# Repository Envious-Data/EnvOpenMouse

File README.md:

# EnvOpenMouse
 An Open-source mouse for the UK market.
 
### Why?

A lot of friends of mine would like something like a ploopyco mouse but there arent such options avaliable here in the UK and even then custom mouses as a whole is just not very popular.

This will be a open source mouse utilizting the PMW3360 and RP2040.

- Why the RP2040? Why not I say
- Why PMW3360 - its easiest to get and is well known by the community meaning resources are avaliable.

### To do
- Need to verify fit of everything
- firmware
- 3d printable housing
- housing/shell maybe can be made of other matierals
- perhaps write a guide on how to order and get everything made
- contact some vendors to sell this through for those who dont want self assembly

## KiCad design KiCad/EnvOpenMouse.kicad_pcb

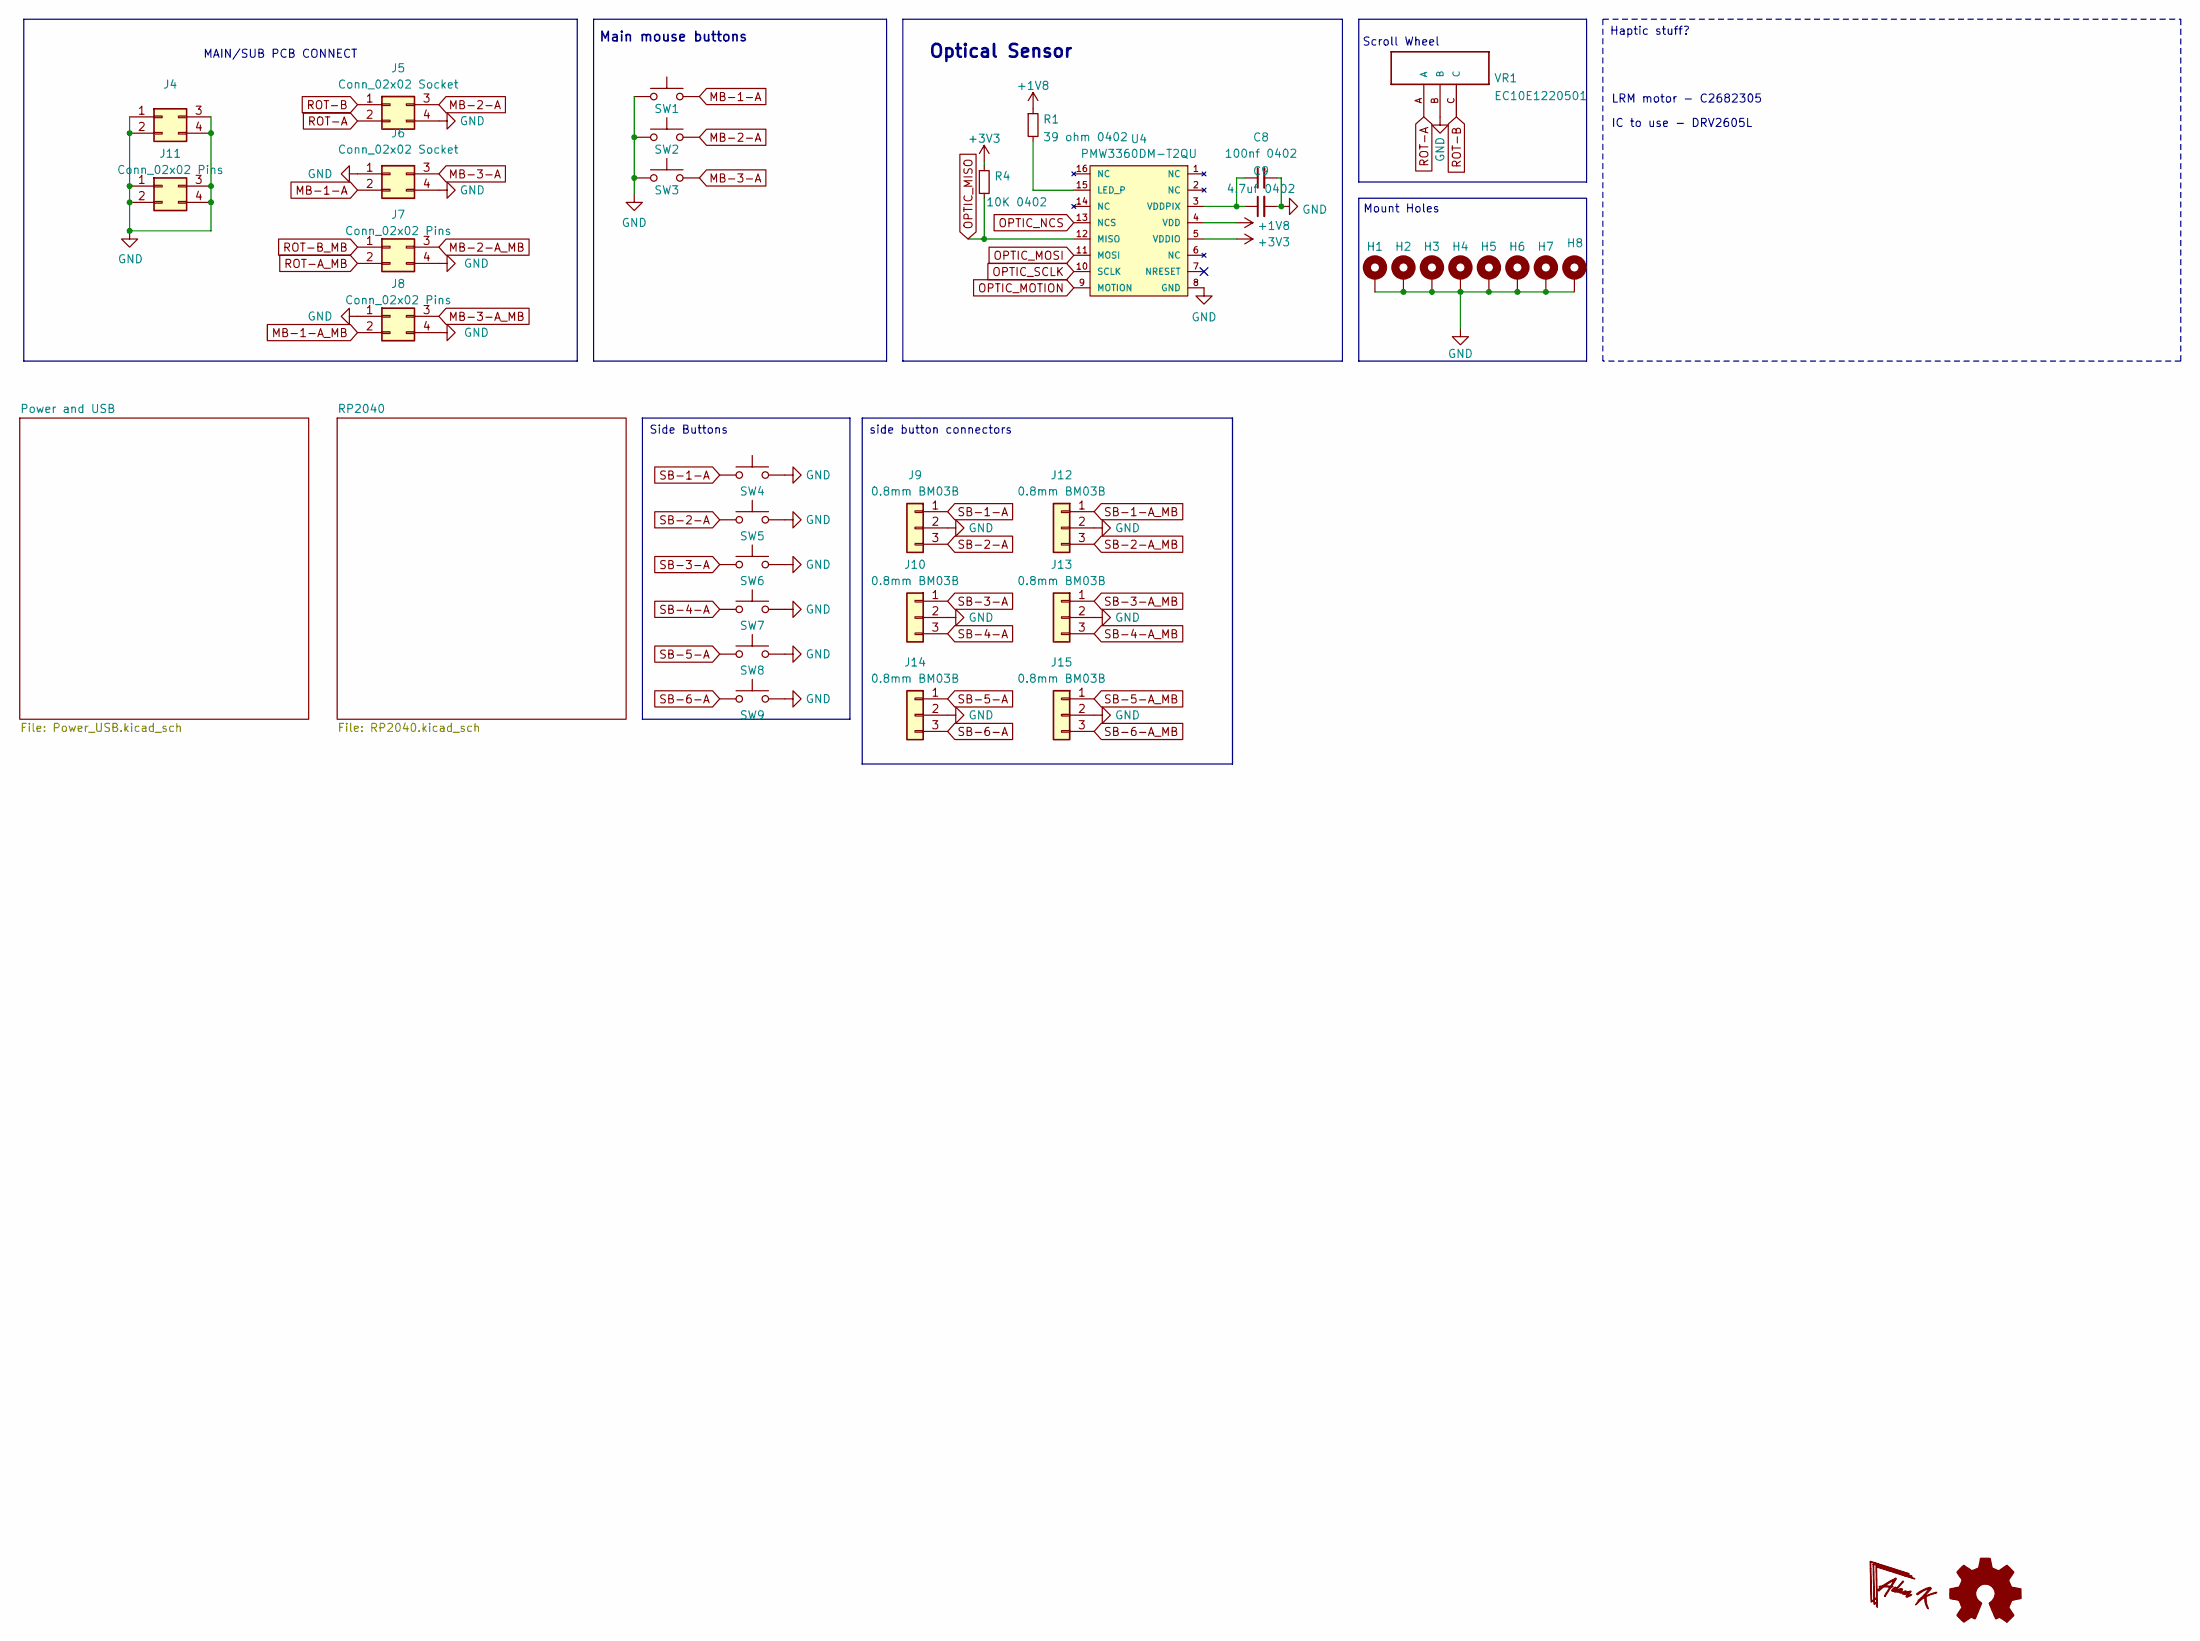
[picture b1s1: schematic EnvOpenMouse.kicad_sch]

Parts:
C8: 100nf 0402; C_0402_1005Metric
C9: 4.7uf 0402; C_0402_1005Metric
H1, H2, H3, H4, H5, H6, H7, H8: MountingHole_Pad; MountingHole_2.2mm_M2
J4: Conn_02x02 Socket; PinSocket_1x02_P1.27mm_Vertical
J5, J6: Conn_02x02 Socket; PinSocket_2x02_P1.27mm_Vertical
J7, J8: Conn_02x02 Pins; PinHeader_2x02_P1.27mm_Vertical
J9, J10, J12, J13, J14, J15: 0.8mm BM03B; JST_SUR_BM03B-SURS-TF_1x03-1MP_P0.80mm_Vertical
J11: Conn_02x02 Pins; PinHeader_1x02_P1.27mm_Vertical
R1: 39 ohm 0402; R_0402_1005Metric
R4: 10K 0402; R_0402_1005Metric
SW1, SW2, SW3: Kailh GM switch; MouseSwitch
SW4, SW5, SW6, SW7, SW8, SW9: B3U-1000P; SW_SPST_B3U-1000P
U4: PMW3360DM-T2QU; DIP-16_W10.16mm
VR1: EC10E1220501; TRIM_EC10E1220501

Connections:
+1V8: R1.1, U4.4 (VDD); also elsewhere on the board
+3V3: R4.1, U4.5 (VDDIO); also elsewhere on the board
GND: C8.2, C9.2, H1.1, H2.1, H3.1, H4.1, H5.1, H6.1, H7.1, H8.1, J4.1, J4.2, J4.3, J4.4, J5.4, J6.1, J6.4, J7.4, J8.1, J8.4, J9.2, J10.2, J11.1, J11.2, J11.3, J11.4, J12.2, J13.2, J14.2, J15.2, SW1.1, SW2.1, SW3.1, SW4.1, SW5.1, SW6.1, SW7.1, SW8.1, SW9.1, U4.8 (GND), VR1.B; also elsewhere on the board
MB-1-A: J6.2, SW1.2
MB-1-A_MB: J8.2; also elsewhere on the board
MB-2-A: J5.3, SW2.2
MB-2-A_MB: J7.3; also elsewhere on the board
MB-3-A: J6.3, SW3.2
MB-3-A_MB: J8.3; also elsewhere on the board
unnamed: R1.2, U4.15 (LED_P)
unnamed: C8.1, C9.1, U4.3 (VDDPIX)
OPTIC_MISO: R4.2, U4.12 (MISO); also elsewhere on the board
OPTIC_MOSI: U4.11 (MOSI); also elsewhere on the board
OPTIC_MOTION: U4.9 (MOTION); also elsewhere on the board
OPTIC_NCS: U4.13 (NCS); also elsewhere on the board
OPTIC_SCLK: U4.10 (SCLK); also elsewhere on the board
ROT-A: J5.2, VR1.A
ROT-A_MB: J7.2; also elsewhere on the board
ROT-B: J5.1, VR1.C
ROT-B_MB: J7.1; also elsewhere on the board
SB-1-A: J9.1, SW4.2
SB-1-A_MB: J12.1; also elsewhere on the board
SB-2-A: J9.3, SW5.2
SB-2-A_MB: J12.3; also elsewhere on the board
SB-3-A: J10.1, SW6.2
SB-3-A_MB: J13.1; also elsewhere on the board
SB-4-A: J10.3, SW7.2
SB-4-A_MB: J13.3; also elsewhere on the board
SB-5-A: J14.1, SW8.2
SB-5-A_MB: J15.1; also elsewhere on the board
SB-6-A: J14.3, SW9.2
SB-6-A_MB: J15.3; also elsewhere on the board

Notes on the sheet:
Side Buttons
side button connectors
Haptic stuff?
MAIN/SUB PCB CONNECT
Scroll Wheel
LRM motor - C2682305
Main mouse buttons
IC to use - DRV2605L
Optical Sensor
Mount Holes

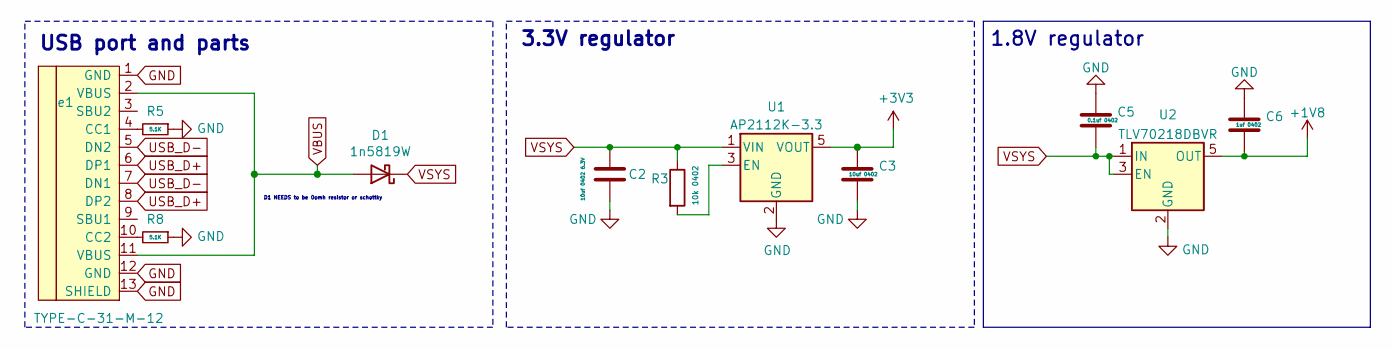
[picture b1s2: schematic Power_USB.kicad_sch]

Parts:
C2: 10uf 0402 6.3V; C_0402_1005Metric
C3: 10uf 0402; C_0402_1005Metric
C5: 0.1uf 0402; C_0402_1005Metric
C6: 1uf 0402; C_0402_1005Metric
D1: 1n5819W; D_SOD-123
R3: 10k 0402; R_0402_1005Metric
R5, R8: 5.1K; R_0402_1005Metric
U1: AP2112K-3.3; SOT-23-5
U2: TLV70218DBVR; SOT-23-5
e1: TYPE-C-31-M-12; HRO-TYPE-C-31-M-12

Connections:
+1V8: C6.2, U2.5 (OUT); also elsewhere on the board
+3V3: C3.1, U1.5 (VOUT); also elsewhere on the board
GND: C2.2, C3.2, C5.1, C6.1, R5.1, R8.1, U1.2 (GND), U2.2 (GND), e1.1 (GND), e1.12 (GND), e1.13 (SHIELD); also elsewhere on the board
unnamed: R3.2, U1.3 (EN)
unnamed: R5.2, e1.4 (CC1)
unnamed: R8.2, e1.10 (CC2)
USB_D+: e1.6 (DP1), e1.8 (DP2); also elsewhere on the board
USB_D-: e1.5 (DN2), e1.7 (DN1); also elsewhere on the board
VBUS: D1.2 (A), e1.2 (VBUS), e1.11 (VBUS)
VSYS: C2.1, C5.2, D1.1 (K), R3.1, U1.1 (VIN), U2.1 (IN), U2.3 (EN)

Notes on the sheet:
1.8V regulator
3.3V regulator
USB port and parts
D1 NEEDS to be 0omh resistor or schottky

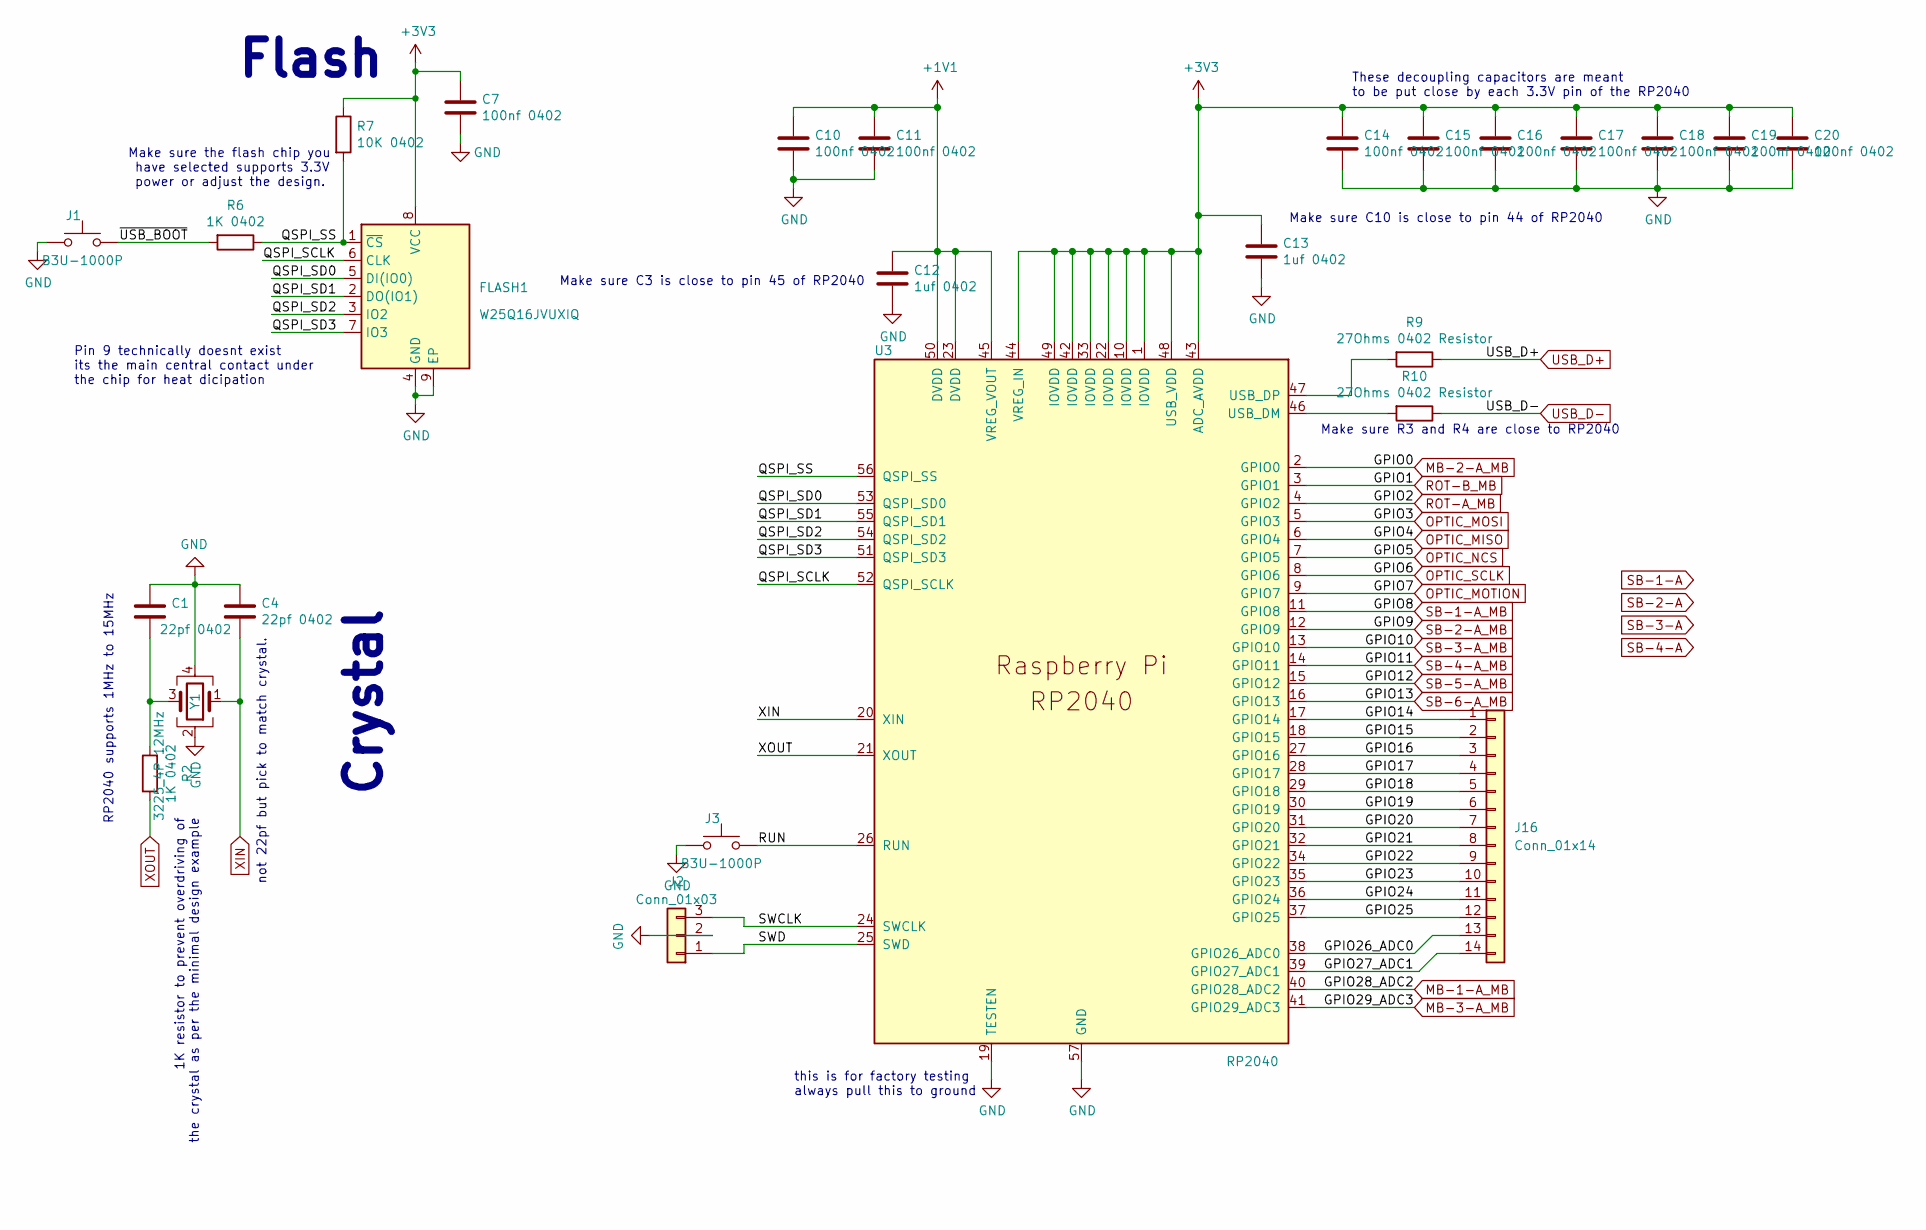
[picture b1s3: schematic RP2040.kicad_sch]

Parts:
C1, C4: 22pf 0402; C_0402_1005Metric
C7, C10, C11, C14, C15, C16, C17, C18, C19, C20: 100nf 0402; C_0402_1005Metric
C12, C13: 1uf 0402; C_0402_1005Metric
FLASH1: W25Q16JVUXIQ; SON-8-1EP_3x2mm_P0.5mm_EP1.4x1.6mm
J1, J3: B3U-1000P; SW_Push_SPST_NO_Alps_SKRK
J2: Conn_01x03; PinHeader_1x03_P1.27mm_Vertical
J16: Conn_01x14; PinHeader_1x14_P1.00mm_Vertical
R2, R6: 1K 0402; R_0402_1005Metric
R7: 10K 0402; R_0402_1005Metric
R9, R10: 27Ohms 0402 Resistor; C_0402_1005Metric
U3: RP2040; RP2040-QFN-56
Y1: 3225_4P 12MHz; Crystal_SMD_3225-4Pin_3.2x2.5mm

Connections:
+1V1: C10.1, C11.1, C12.1, U3.23 (DVDD), U3.45 (VREG_VOUT), U3.50 (DVDD)
+3V3: C7.1, C13.1, C14.1, C15.1, C16.1, C17.1, C18.1, C19.1, C20.1, FLASH1.8 (VCC), R7.1, U3.1 (IOVDD), U3.10 (IOVDD), U3.22 (IOVDD), U3.33 (IOVDD), U3.42 (IOVDD), U3.43 (ADC_AVDD), U3.44 (VREG_IN), U3.48 (USB_VDD), U3.49 (IOVDD); also elsewhere on the board
/RP2040/GPIO14: J16.1, U3.17 (GPIO14)
/RP2040/GPIO15: J16.2, U3.18 (GPIO15)
/RP2040/GPIO16: J16.3, U3.27 (GPIO16)
/RP2040/GPIO17: J16.4, U3.28 (GPIO17)
/RP2040/GPIO18: J16.5, U3.29 (GPIO18)
/RP2040/GPIO19: J16.6, U3.30 (GPIO19)
/RP2040/GPIO20: J16.7, U3.31 (GPIO20)
/RP2040/GPIO21: J16.8, U3.32 (GPIO21)
/RP2040/GPIO22: J16.9, U3.34 (GPIO22)
/RP2040/GPIO23: J16.10, U3.35 (GPIO23)
/RP2040/GPIO24: J16.11, U3.36 (GPIO24)
/RP2040/GPIO25: J16.12, U3.37 (GPIO25)
/RP2040/GPIO26_ADC0: J16.13, U3.38 (GPIO26_ADC0)
/RP2040/GPIO27_ADC1: J16.14, U3.39 (GPIO27_ADC1)
/RP2040/QSPI_SCLK: FLASH1.6 (CLK), U3.52 (QSPI_SCLK)
/RP2040/QSPI_SD0: FLASH1.5 (DI(IO0)), U3.53 (QSPI_SD0)
/RP2040/QSPI_SD1: FLASH1.2 (DO(IO1)), U3.55 (QSPI_SD1)
/RP2040/QSPI_SD2: FLASH1.3 (IO2), U3.54 (QSPI_SD2)
/RP2040/QSPI_SD3: FLASH1.7 (IO3), U3.51 (QSPI_SD3)
/RP2040/QSPI_SS: FLASH1.1 (~CS), R6.1, R7.2, U3.56 (QSPI_SS)
/RP2040/RUN: J3.1, U3.26 (RUN)
/RP2040/SWCLK: J2.3, U3.24 (SWCLK)
/RP2040/SWD: J2.1, U3.25 (SWD)
/RP2040/~USB_BOOT: J1.1, R6.2
GND: C1.1, C4.1, C7.2, C10.2, C11.2, C12.2, C13.2, C14.2, C15.2, C16.2, C17.2, C18.2, C19.2, C20.2, FLASH1.4 (GND), FLASH1.9 (EP), J1.2, J2.2, J3.2, U3.19 (TESTEN), U3.57 (GND), Y1.2, Y1.4; also elsewhere on the board
MB-1-A_MB: U3.40 (GPIO28_ADC2); also elsewhere on the board
MB-2-A_MB: U3.2 (GPIO0); also elsewhere on the board
MB-3-A_MB: U3.41 (GPIO29_ADC3); also elsewhere on the board
unnamed: C1.2, R2.2, Y1.3
unnamed: R10.2, U3.46 (USB_DM)
unnamed: R9.2, U3.47 (USB_DP)
OPTIC_MISO: U3.6 (GPIO4); also elsewhere on the board
OPTIC_MOSI: U3.5 (GPIO3); also elsewhere on the board
OPTIC_MOTION: U3.9 (GPIO7); also elsewhere on the board
OPTIC_NCS: U3.7 (GPIO5); also elsewhere on the board
OPTIC_SCLK: U3.8 (GPIO6); also elsewhere on the board
ROT-A_MB: U3.4 (GPIO2); also elsewhere on the board
ROT-B_MB: U3.3 (GPIO1); also elsewhere on the board
SB-1-A_MB: U3.11 (GPIO8); also elsewhere on the board
SB-2-A_MB: U3.12 (GPIO9); also elsewhere on the board
SB-3-A_MB: U3.13 (GPIO10); also elsewhere on the board
SB-4-A_MB: U3.14 (GPIO11); also elsewhere on the board
SB-5-A_MB: U3.15 (GPIO12); also elsewhere on the board
SB-6-A_MB: U3.16 (GPIO13); also elsewhere on the board
USB_D+: R9.1; also elsewhere on the board
USB_D-: R10.1; also elsewhere on the board
XIN: C4.2, U3.20 (XIN), Y1.1
XOUT: R2.1, U3.21 (XOUT)

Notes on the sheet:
Make sure C10 is close to pin 44 of RP2040
1K resistor to prevent overdriving of the crystal as per the minimal design example
Crystal
Make sure R3 and R4 are close to RP2040
this is for factory testing always pull this to ground
Make sure C3 is close to pin 45 of RP2040
Pin 9 technically doesnt exist its the main central contact under the chip for heat dicipation
not 22pf but pick to match crystal.
These decoupling capacitors are meant to be put close by each 3.3V pin of the RP2040
Make sure the flash chip you have selected supports 3.3V power or adjust the design.
Flash
RP2040 supports 1MHz to 15MHz

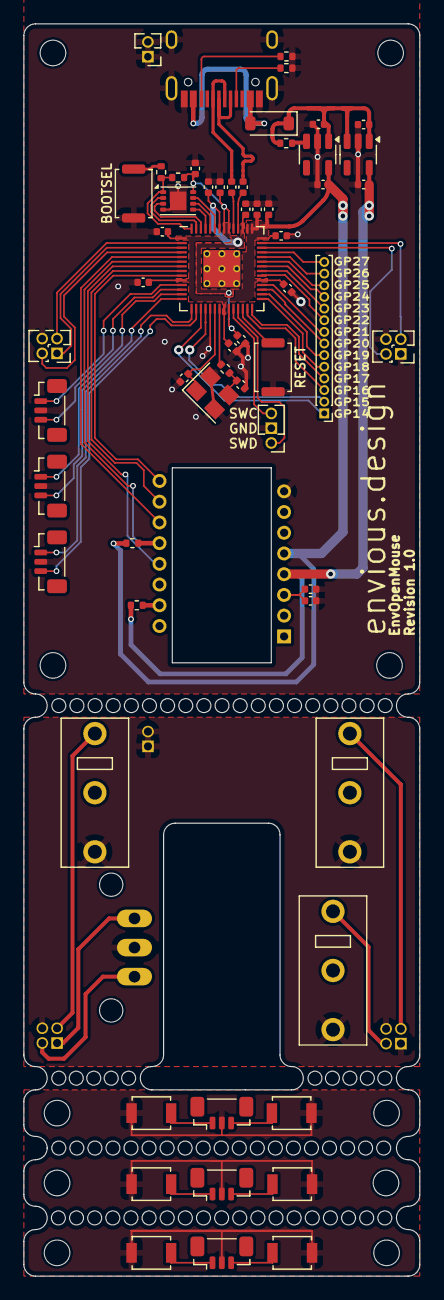
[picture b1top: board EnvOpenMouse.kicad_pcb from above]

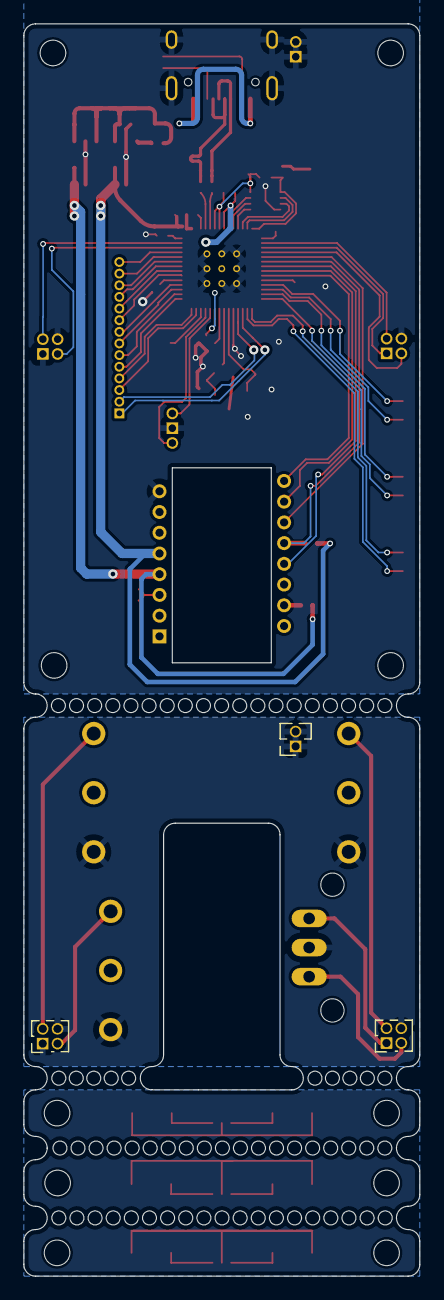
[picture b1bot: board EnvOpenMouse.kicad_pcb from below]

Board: 2 copper layers, 34.0 x 107.5 mm, 74 parts (3 on the bottom side), 69 nets.

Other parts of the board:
H5#2, H6#2: MountingHole_Pad; MountingHole_2.2mm_M2

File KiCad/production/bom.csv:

Designator,Footprint,Quantity,Value,LCSC Part #
"C1, C4",0402,2,22pf 0402, 
"C10, C11, C14, C15, C16, C17, C18, C19, C20, C8",0402,10,100nf 0402,
"C12, C13, C6",0402,3,1uf 0402,
C2,0402,1,10uf 0402 6.3V,
C3,0402,1,10uf 0402,
C5,0402,1,0.1uf 0402,
C7,0402,1,100nf 0402, 
C9,0402,1,4.7uf 0402,
D1,D_SOD-123,1,1n4002W,
FLASH1,SON-8-1EP_3x2mm_P0.5mm_EP1.4x1.6mm,1,W25Q16JVUXIQ,
"H1, H2, H3, H4, H5_2, H5, H6_2, H6, H7, H8",MountingHole_2.2mm_M2,10,MountingHole_Pad,
J1,SW_Push_SPST_NO_Alps_SKRK,1,Button, 
"J10, J12, J13, J14, J15, J9",JST_SUR_BM03B-SURS-TF_1x03-1MP_P0.80mm_Vertical,6,0.8mm BM03B,
"J11, J4",PinHeader_1x02_P1.27mm_Vertical,2,Conn_02x02_Top_Bottom,
J16,PinHeader_1x14_P1.00mm_Vertical,1,Conn_01x14,
J2,PinHeader_1x03_P1.27mm_Vertical,1,Conn_01x03,
J3,SW_Push_SPST_NO_Alps_SKRK,1,Button,
"J5, J6, J7, J8",PinHeader_2x02_P1.27mm_Vertical,4,Conn_02x02_Top_Bottom,
R1,0402,1,39 ohm 0402,
R10,0402,1,27Ohms 0402 Resistor,
"R2, R6",0402,2,1K 0402, 
"R3, R4",0402,2,10k 0402,
"R5, R8",0402,2,5.1K,
R7,0402,1,10K 0402,  
R9,0402,1,27Ohms  0402 Resistor,
"SW1, SW2, SW3",MouseSwitch,3,SW_Push_SPDT,
"SW4, SW5, SW6, SW7, SW8, SW9",SW_SPST_B3U-1000P,6,SW_Push_SPDT,
U1,SOT-23-5,1,AP2112K-3.3,
U2,SOT-23-5,1,TLV70218DBVR,
U3,RP2040-QFN-56,1,RP2040,
U4,DIP-16_W10.16mm,1,PMW3360DM-T2QU,
VR1,TRIM_EC10E1220501,1,EC10E1220501,
Y1,Crystal_SMD_3225-4Pin_3.2x2.5mm,1,3225_4P 12MHz, 
e1,HRO-TYPE-C-31-M-12,1,TYPE-C-31-M-12,

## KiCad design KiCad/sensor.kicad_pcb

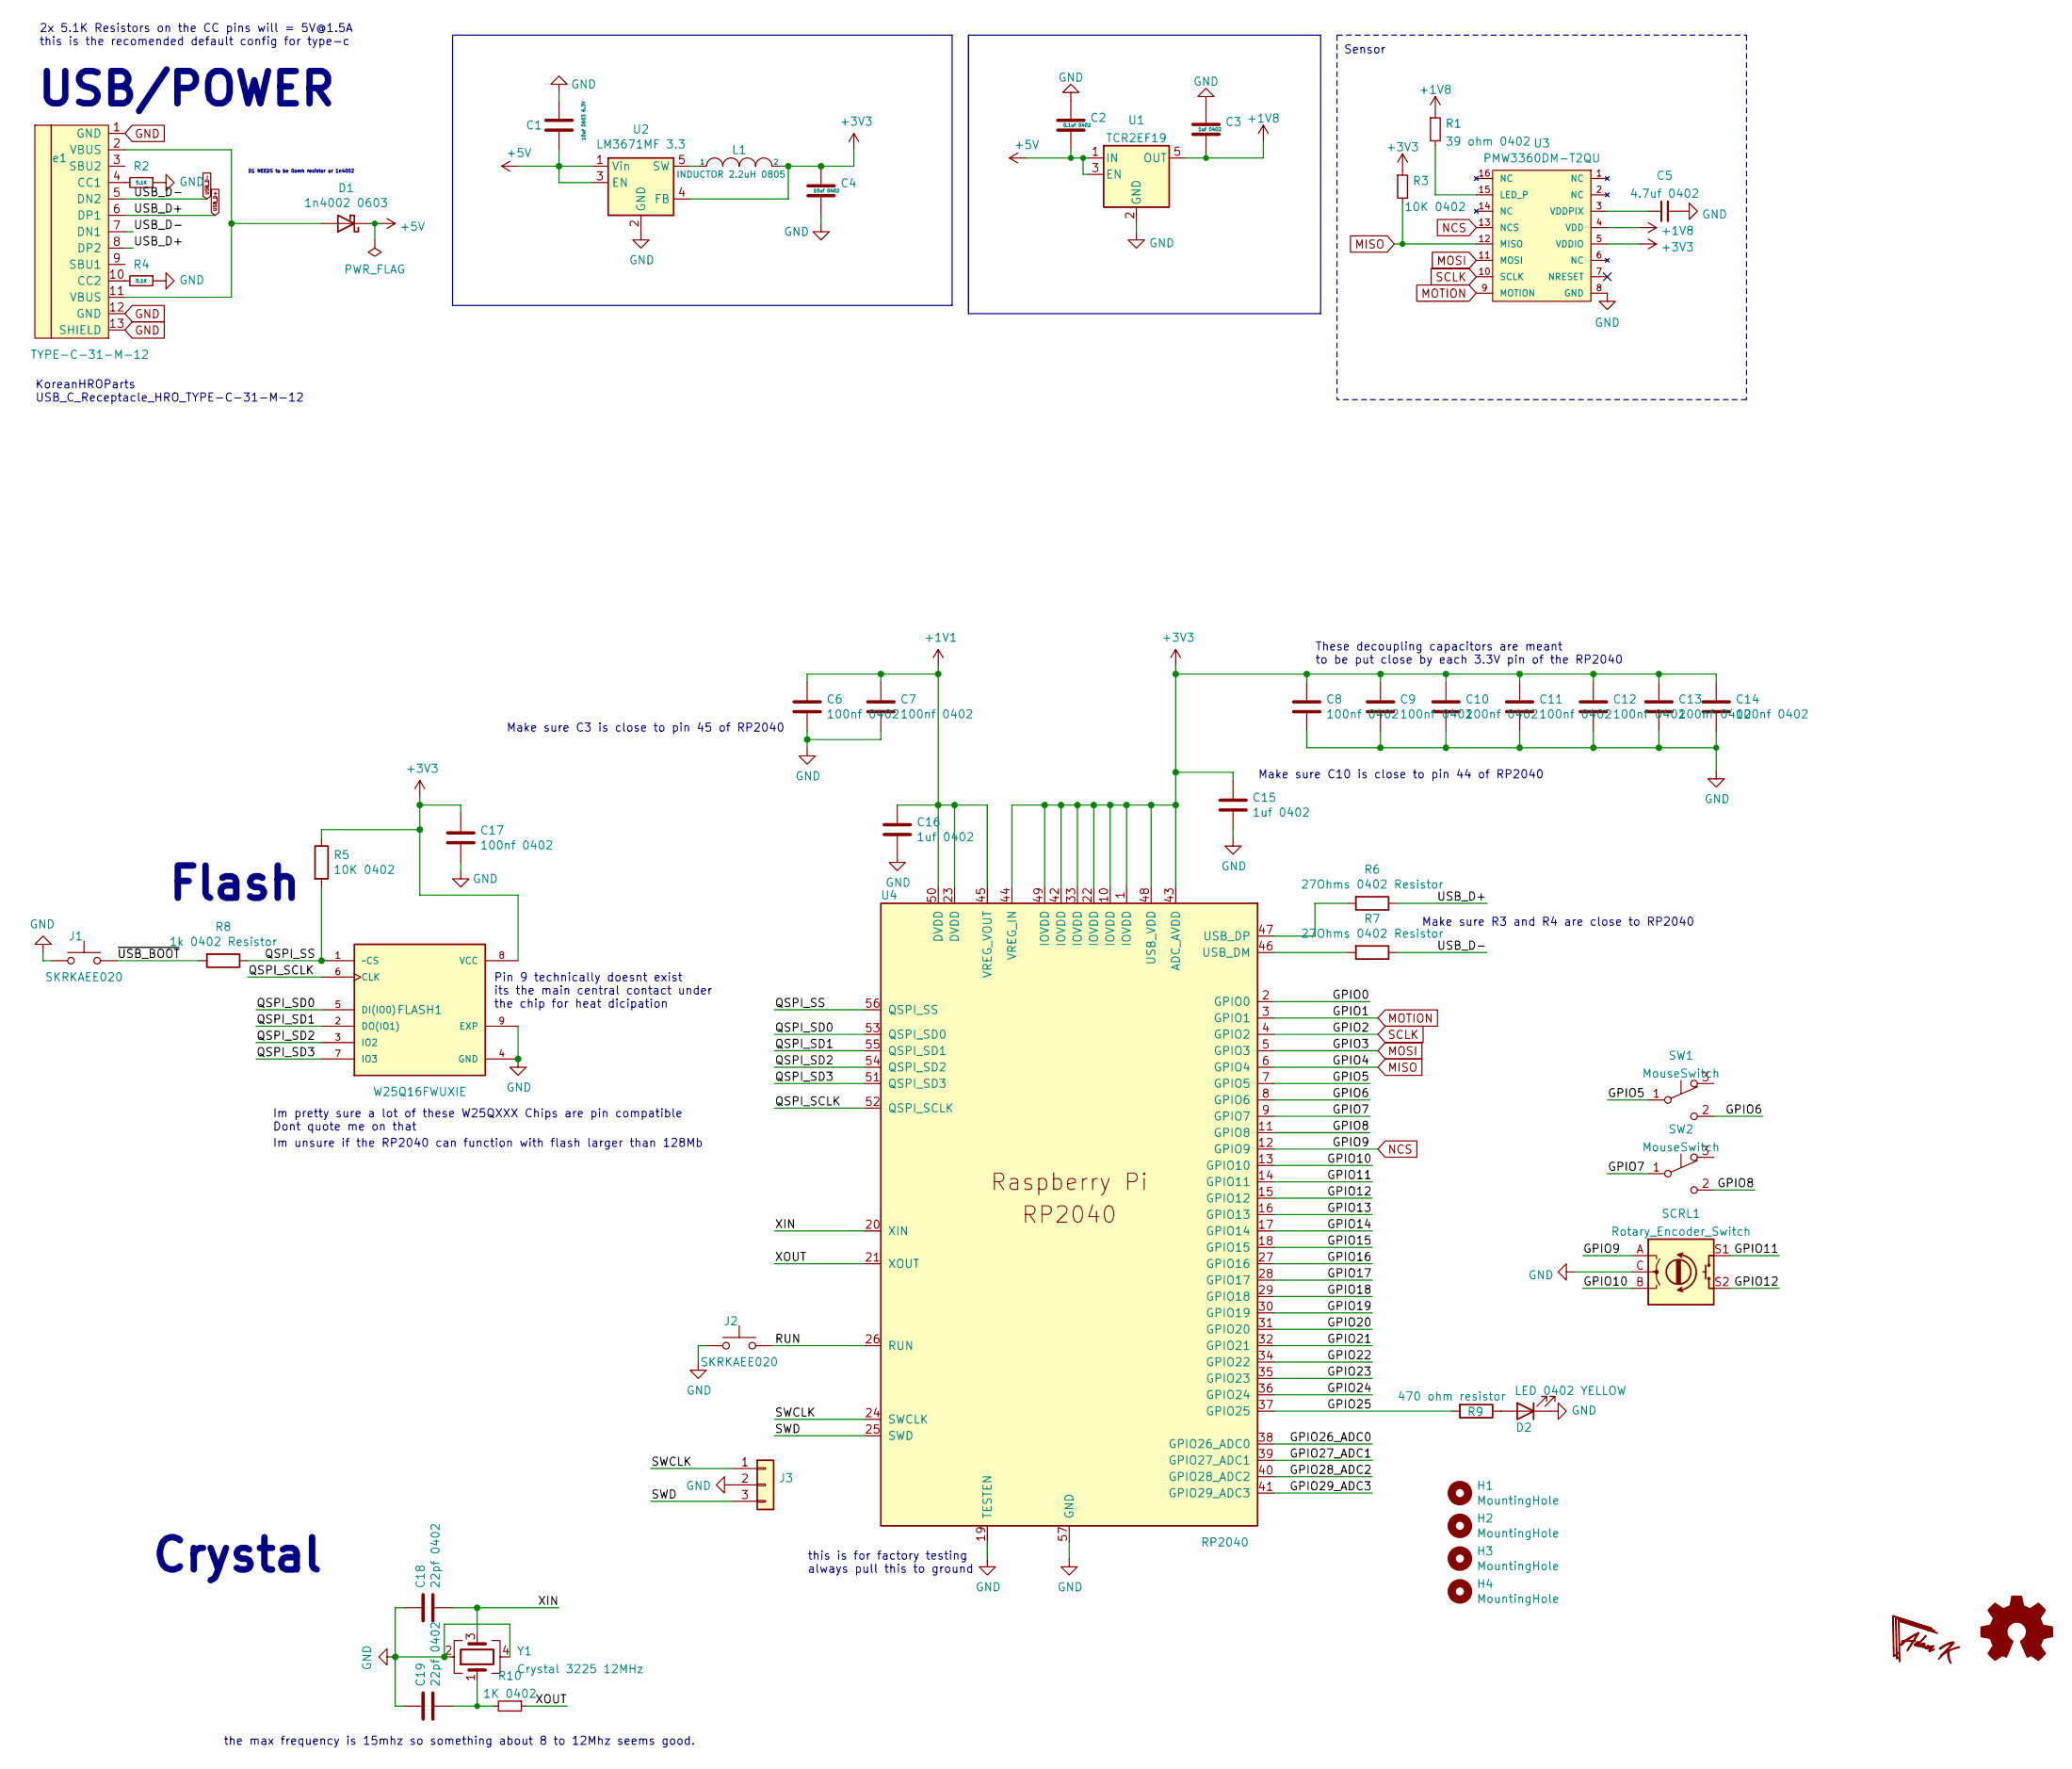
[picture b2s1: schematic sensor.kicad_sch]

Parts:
C1: 10uf 0603 6.3V; C_0603_1608Metric
C2: 0.1uf 0402; C_0402_1005Metric
C3, C15, C16: 1uf 0402; C_0402_1005Metric
C4: 10uf 0402; C_0402_1005Metric
C5: 4.7uf 0402; C_0402_1005Metric
C6, C7, C8, C9, C10, C11, C12, C13, C14, C17: 100nf 0402; C_0402_1005Metric
C18, C19: 22pf 0402; C_0402_1005Metric
D1: 1n4002 0603; D_0603_1608Metric
D2: LED 0402 YELLOW; LED_0402_1005Metric
FLASH1: W25Q16FWUXIE; SON-8-1EP_3x2mm_P0.5mm_EP1.4x1.6mm
H1, H2, H3, H4: MountingHole; MountingHole_2.2mm_M2
J1, J2: SKRKAEE020; SW_Push_SPST_NO_Alps_SKRK
J3: Conn_01x03_Male; PinHeader_1x03_P2.54mm_Vertical
L1: INDUCTOR 2.2uH 0805; L_0805_2012Metric
R1: 39 ohm 0402; R_0402_1005Metric
R2, R4: 5.1K; R_0402_1005Metric
R3: 10K 0402; R_0402_1005Metric
R5: 10K 0402; C_0402_1005Metric
R6, R7: 27Ohms 0402 Resistor; C_0402_1005Metric
R8: 1k 0402 Resistor; C_0402_1005Metric
R9: 470 ohm resistor; R_0402_1005Metric
R10: 1K 0402; R_0402_1005Metric
SCRL1: Rotary_Encoder_Switch
SW1, SW2: MouseSwitch
U1: TCR2EF19; SOT-23-5
U2: LM3671MF 3.3; SOT-23-5
U3: PMW3360DM-T2QU; DIP-16_W10.16mm
U4: RP2040; RP2040-QFN-56
Y1: Crystal 3225 12MHz; Crystal_SMD_3225-4Pin_3.2x2.5mm
e1: TYPE-C-31-M-12; HRO-TYPE-C-31-M-12-Assembly

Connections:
+1V1: C6.1, C7.1, C16.1, U4.23 (DVDD), U4.45 (VREG_VOUT), U4.50 (DVDD)
+1V8: C3.2, R1.1, U1.5 (OUT), U3.4 (VDD)
+3V3: C4.1, C8.1, C9.1, C10.1, C11.1, C12.1, C13.1, C14.1, C15.1, C17.1, FLASH1.8 (VCC), L1.2, R3.1, R5.1, U2.4 (FB), U3.5 (VDDIO), U4.1 (IOVDD), U4.10 (IOVDD), U4.22 (IOVDD), U4.33 (IOVDD), U4.42 (IOVDD), U4.43 (ADC_AVDD), U4.44 (VREG_IN), U4.48 (USB_VDD), U4.49 (IOVDD)
+5V: C1.1, C2.2, D1.1 (K), U1.1 (IN), U1.3 (EN), U2.1 (Vin), U2.3 (EN)
/GPIO0: U4.2 (GPIO0)
/GPIO5: SW1.1 (A), U4.7 (GPIO5)
/GPIO6: SW1.2 (B), U4.8 (GPIO6)
/GPIO7: SW2.1 (A), U4.9 (GPIO7)
/GPIO8: SW2.2 (B), U4.11 (GPIO8)
/GPIO10: SCRL1.B, U4.13 (GPIO10)
/GPIO11: SCRL1.S1, U4.14 (GPIO11)
/GPIO12: SCRL1.S2, U4.15 (GPIO12)
/GPIO13: U4.16 (GPIO13)
/GPIO14: U4.17 (GPIO14)
/GPIO15: U4.18 (GPIO15)
/GPIO16: U4.27 (GPIO16)
/GPIO17: U4.28 (GPIO17)
/GPIO18: U4.29 (GPIO18)
/GPIO19: U4.30 (GPIO19)
/GPIO20: U4.31 (GPIO20)
/GPIO21: U4.32 (GPIO21)
/GPIO22: U4.34 (GPIO22)
/GPIO23: U4.35 (GPIO23)
/GPIO24: U4.36 (GPIO24)
/GPIO25: R9.2, U4.37 (GPIO25)
/GPIO26_ADC0: U4.38 (GPIO26_ADC0)
/GPIO27_ADC1: U4.39 (GPIO27_ADC1)
/GPIO28_ADC2: U4.40 (GPIO28_ADC2)
/GPIO29_ADC3: U4.41 (GPIO29_ADC3)
/QSPI_SCLK: FLASH1.6 (CLK), U4.52 (QSPI_SCLK)
/QSPI_SD0: FLASH1.5 (DI(IO0)), U4.53 (QSPI_SD0)
/QSPI_SD1: FLASH1.2 (DO(IO1)), U4.55 (QSPI_SD1)
/QSPI_SD2: FLASH1.3 (IO2), U4.54 (QSPI_SD2)
/QSPI_SD3: FLASH1.7 (IO3), U4.51 (QSPI_SD3)
/QSPI_SS: FLASH1.1 (~CS), R5.2, R8.1, U4.56 (QSPI_SS)
/RUN: J2.1, U4.26 (RUN)
/SWCLK: J3.1, U4.24 (SWCLK)
/SWD: J3.3, U4.25 (SWD)
/XIN: C18.2, U4.20 (XIN), Y1.3
/XOUT: R10.1, U4.21 (XOUT)
/~USB_BOOT: J1.1, R8.2
GND: C1.2, C2.1, C3.1, C4.2, C5.2, C6.2, C7.2, C8.2, C9.2, C10.2, C11.2, C12.2, C13.2, C14.2, C15.2, C16.2, C17.2, C18.1, C19.1, D2.1 (K), FLASH1.4 (GND), FLASH1.9 (EXP), J1.2, J2.2, J3.2, R2.1, R4.1, U1.2 (GND), U2.2 (GND), U3.8 (GND), U4.19 (TESTEN), U4.57 (GND), Y1.2, Y1.4, e1.1 (GND), e1.12 (GND), e1.13 (SHIELD)
MISO: R3.2, U3.12 (MISO), U4.6 (GPIO4)
MOSI: U3.11 (MOSI), U4.5 (GPIO3)
MOTION: U3.9 (MOTION), U4.3 (GPIO1)
NCS: SCRL1.A, U3.13 (NCS), U4.12 (GPIO9)
unnamed: C5.1, U3.3 (VDDPIX)
unnamed: C19.2, R10.2, Y1.1
unnamed: D1.2 (A), e1.2 (VBUS), e1.11 (VBUS)
unnamed: D2.2 (A), R9.1
unnamed: L1.1, U2.5 (SW)
unnamed: R1.2, U3.15 (LED_P)
unnamed: R2.2, e1.4 (CC1)
unnamed: R4.2, e1.10 (CC2)
unnamed: R6.2, U4.47 (USB_DP)
unnamed: R7.2, U4.46 (USB_DM)
SCLK: U3.10 (SCLK), U4.4 (GPIO2)
USB_D+: R6.1, e1.6 (DP1), e1.8 (DP2)
USB_D-: R7.1, e1.5 (DN2), e1.7 (DN1)

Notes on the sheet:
USB/POWER
KoreanHROParts USB_C_Receptacle_HRO_TYPE-C-31-M-12
2x 5.1K Resistors on the CC pins will = 5V@1.5A this is the recomended default config for type-c
Crystal
Flash
the max frequency is 15mhz so something about 8 to 12Mhz seems good.
D1 NEEDS to be 0omh resistor or 1n4002
Im pretty sure a lot of these W25QXXX Chips are pin compatible Dont quote me on that
Im unsure if the RP2040 can function with flash larger than 128Mb
Pin 9 technically doesnt exist its the main central contact under the chip for heat dicipation
Make sure C3 is close to pin 45 of RP2040
this is for factory testing always pull this to ground
Make sure C10 is close to pin 44 of RP2040
These decoupling capacitors are meant to be put close by each 3.3V pin of the RP2040
Sensor
Make sure R3 and R4 are close to RP2040

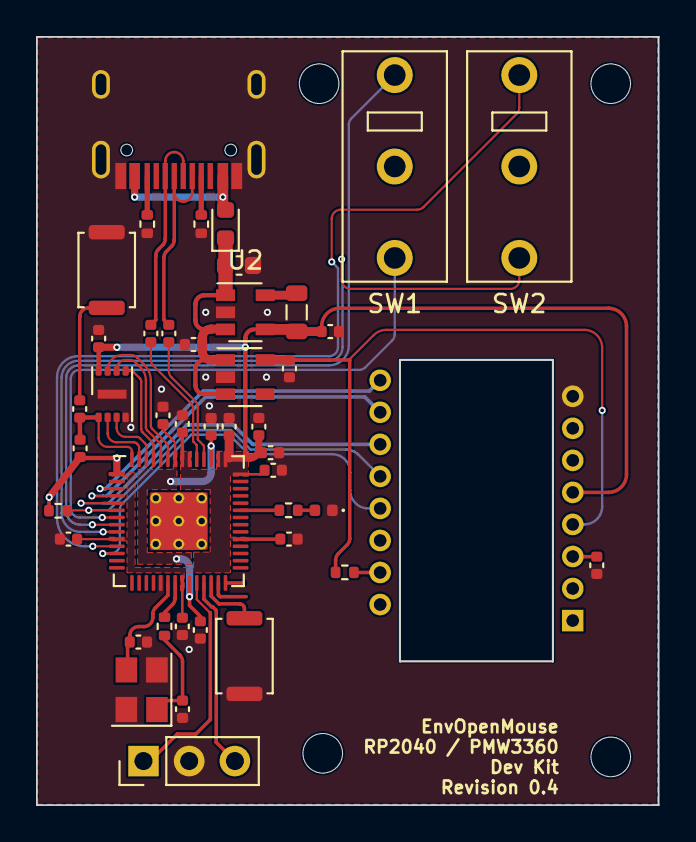
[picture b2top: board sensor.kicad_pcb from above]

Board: 2 copper layers, 34.5 x 42.7 mm, 48 parts (0 on the bottom side), 39 nets.

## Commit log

2021-10-30 Initial commit +1
2021-10-30 added mouse switch footprint.
2021-10-30 added license, some small tweaks and all.
2021-10-30 organized libraries.
2021-10-31 Decided redo PCB
2021-10-31 Fillet :cat2:
2021-10-31 added rotary encoder to the schematic
2021-10-31 Renamed KiCad Project Appropriately
2021-10-31 Updated gitignore to ignore backup folder
2021-10-31 added some GPIO headers
2021-10-31 adjusted silkscreen markings and some traces.
2021-11-22 swapped button bits for some GPIO headers
2022-01-07 decided to overhaul this project a bit
2022-01-09 small fix
2022-01-28 added missing capactor and middle click button.
2022-08-06 Appended RP2040 to board, begin work on Mouse PCB
2022-08-06 routed onboard MCU
2022-08-27 I dont even remember what I changed.
2023-02-08 decided to work on this again | made PCB have reasonableish dimensions and moved mouse buttons to suitable positions
2023-02-08 routed some more traces
2023-02-16 ran traces for parts previously left disconnected and moved about some to improve ease of routing and also shortened PCB down to 94mm along with slimmed width + mount holes
2023-03-03 to do list
2023-03-03 adjusted position of some parts and re-routed related traces, might do that again to compact everything
2023-03-03 Decided to re-design the whole board again but with a pico so perhaps I can fit a PicoW and maybe make a BLE version
2023-03-04 routed and adjusted various traces and component positions
2023-03-13 overhauled design and generated gerbers
2023-03-13 corrected some issues and updated gerbers
2023-03-19 corrected some issues with the design + added fpc/ffc for cirque glidepoint
2023-10-06 commit changes I forgot to commit, unsure of what it contains
2024-04-04 re-worked PCB to remove wireless support and battery charge IC
2024-04-04 forgot to remove some silkscreen
2024-05-16 removed a bunch of headers, added proper zones for 3v3 and 1v1, would like to add 4x side buttons
2024-06-02 redid all traces, adjusted schematic, pinouts, added some side buttons.
2024-06-07 swapped some 3d models
2024-06-18 Added missing connections.
2024-09-12 double checked board and tidied things up.
2024-09-18 downsized main board, added more buttons and respective connector, improved spacing of various power traces
2024-09-18 added header for unused GPIOs
2024-09-18 generated production files
2024-09-19 final cleanups and other fixes
2024-09-23 updated part values, generated production files
2024-09-23 generated fixes production files
